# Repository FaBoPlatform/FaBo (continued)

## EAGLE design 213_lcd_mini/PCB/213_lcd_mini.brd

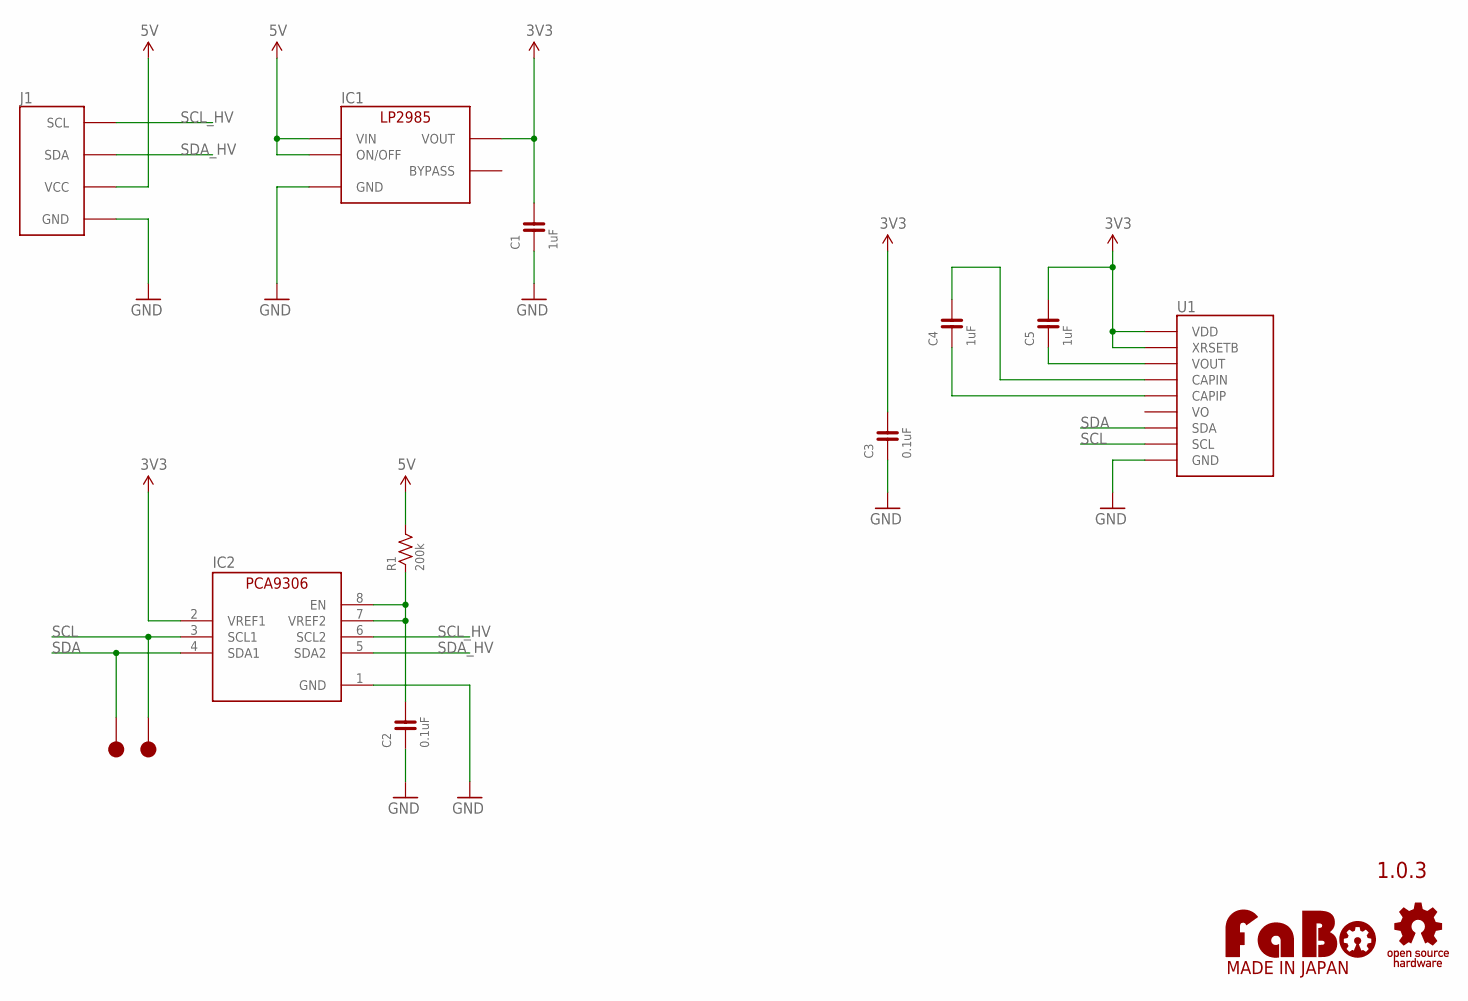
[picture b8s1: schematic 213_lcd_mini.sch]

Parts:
C1, C4, C5: 1uF; 0603
C2, C3: 0.1uF; 0603
IC1: TI-LP2985-33DBVR; TI-LP2985
IC2: PCA9306DQER; X2SON
J1: FABO_BRICK_I2C
R1: 200k; 0603
TP1, TP2: TP-10
U1: AQM0802A
U$2: LOGO_OSHW-M_BOTTOM; LOGO_OSHW_M_BOTTOM
U$3: LOGO_FABO-M; LOGO_FABO_MS

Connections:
3V3: C1.2, C3.2, C5.2, IC1.5 (VOUT), IC2.2 (VREF1), U1.5 (VDD), U1.9 (XRSETB)
5V: IC1.1 (VIN), IC1.3 (ON/OFF), J1.VCC, R1.2
CAPIN: C4.2, U1.3 (CAPIN)
CAPIP: C4.1, U1.4 (CAPIP)
GND: C1.1, C2.1, C3.1, IC1.2 (GND), IC2.1 (GND), J1.GND, U1.6 (GND)
unnamed: C2.2, IC2.7 (VREF2), IC2.8 (EN), R1.1
SCL: IC2.3 (SCL1), TP2.1, U1.8 (SCL)
SCL_HV: IC2.6 (SCL2), J1.SCL
SDA: IC2.4 (SDA1), TP1.1, U1.7 (SDA)
SDA_HV: IC2.5 (SDA2), J1.SDA
VOUT: C5.1, U1.2 (VOUT)

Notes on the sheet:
1.0.3

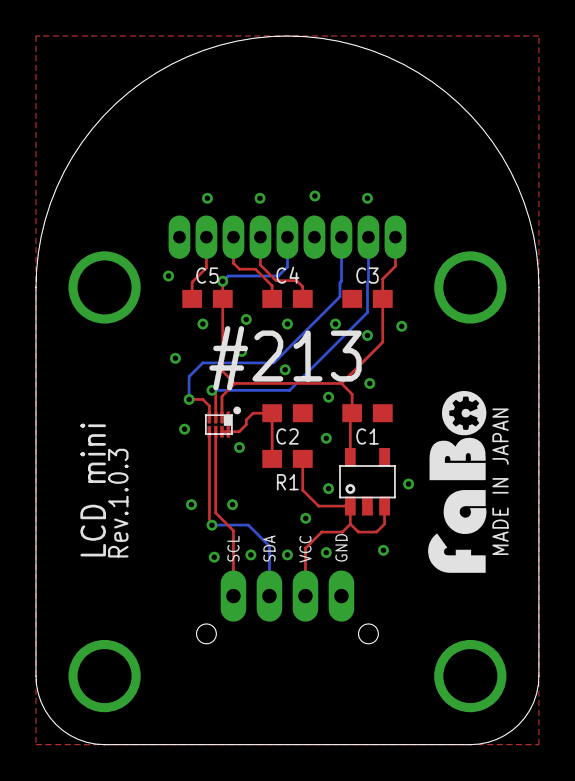
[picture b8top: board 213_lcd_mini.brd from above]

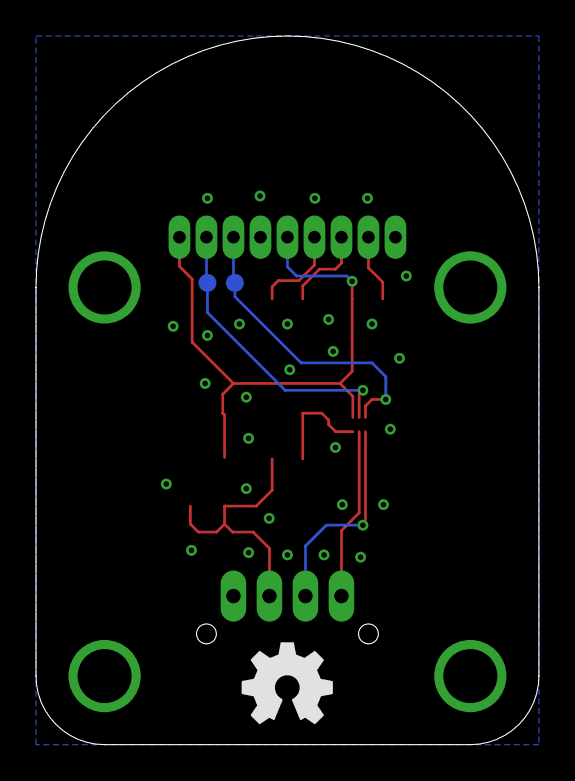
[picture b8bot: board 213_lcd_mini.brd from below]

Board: 2 copper layers, 27.9 x 39.4 mm, 14 parts (2 on the bottom side), 11 nets.
